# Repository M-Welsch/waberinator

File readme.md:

# Waberinator

Ambient LED driver unit for this guy: https://www.deviantart.com/seggos-artworks

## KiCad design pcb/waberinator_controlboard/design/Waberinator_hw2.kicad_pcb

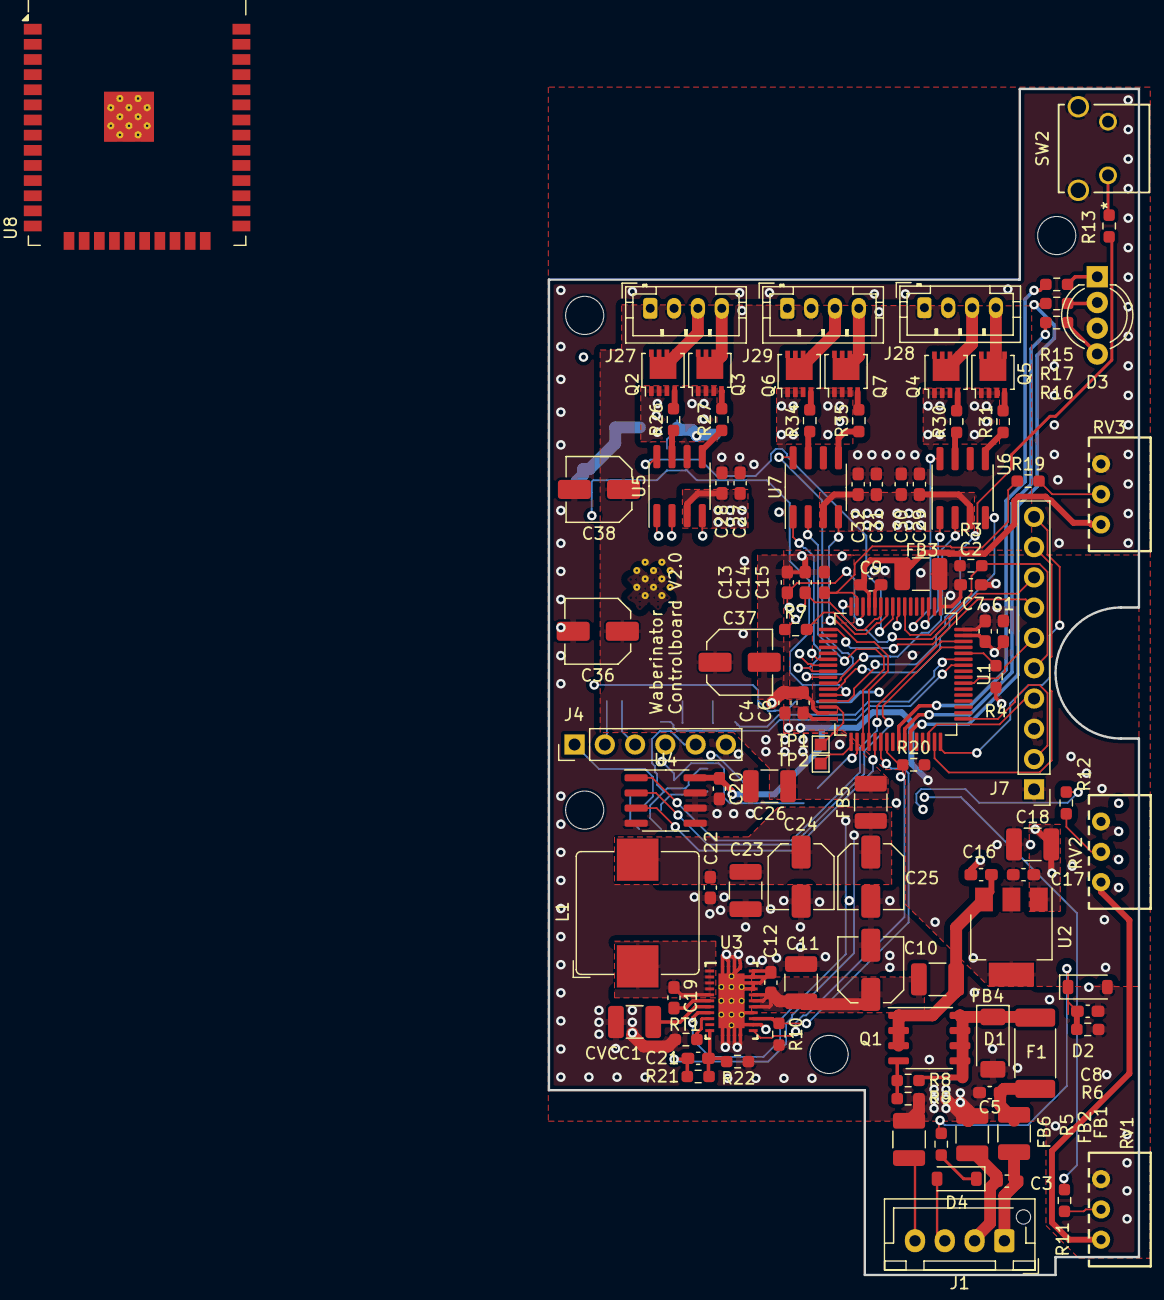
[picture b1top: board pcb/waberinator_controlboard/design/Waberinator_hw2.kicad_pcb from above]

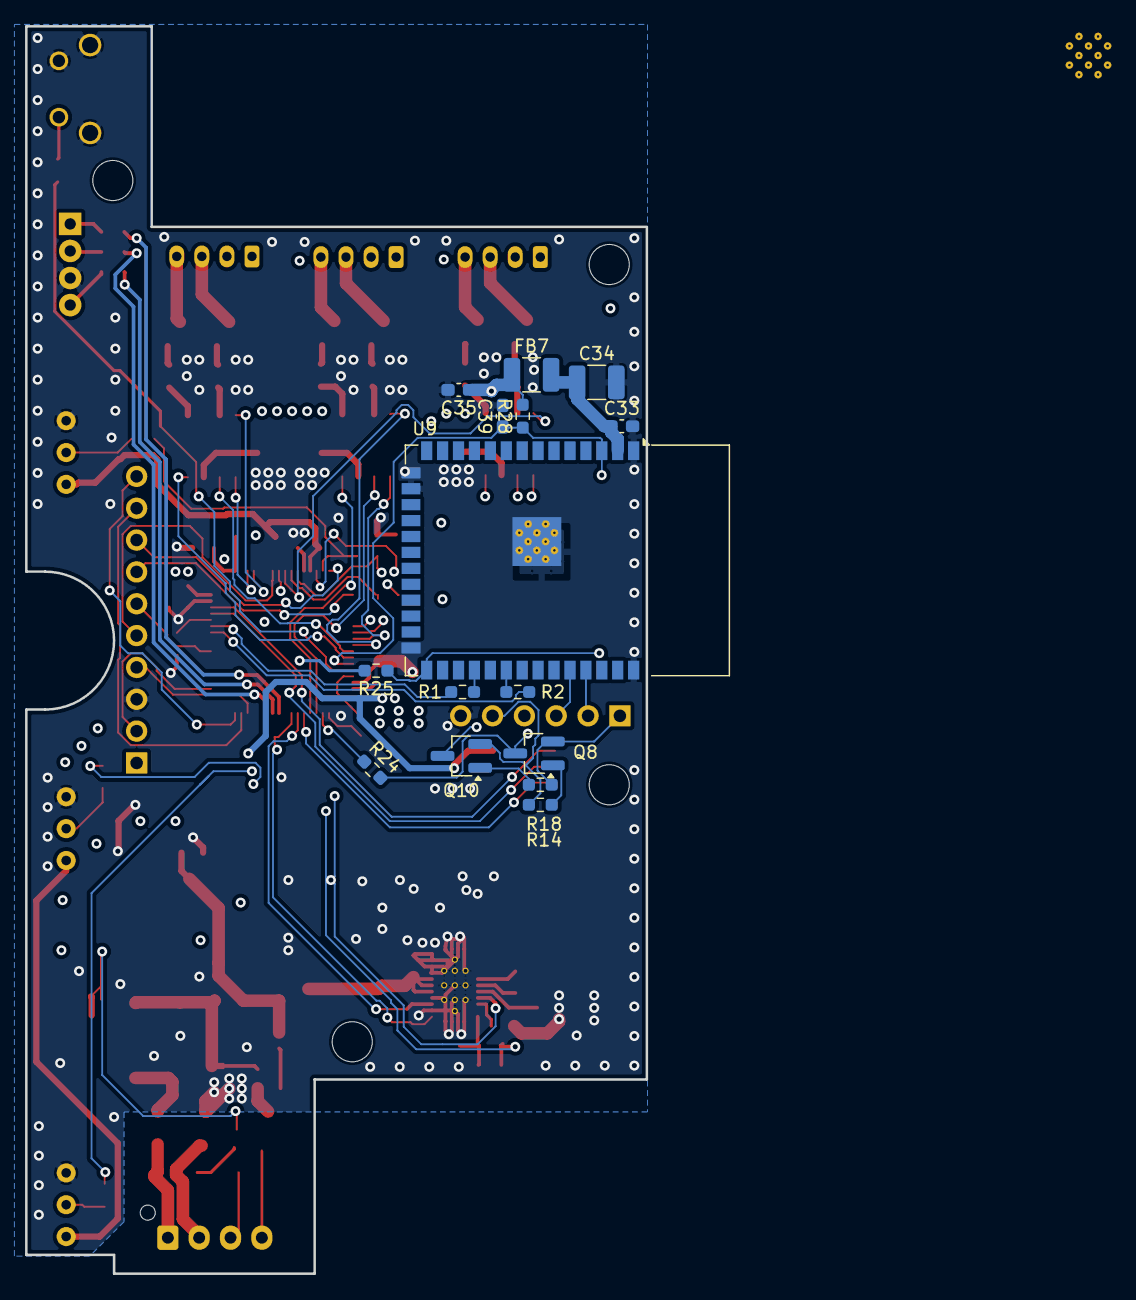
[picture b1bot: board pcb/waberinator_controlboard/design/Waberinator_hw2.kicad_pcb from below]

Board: 4 copper layers, 49.5 x 99.5 mm, 120 parts (15 on the bottom side), 98 nets.

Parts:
C1, C27, C29, C31, C39: 1µF; C_0603_1608Metric_Pad1.08x0.95mm_HandSolder
C2, C4, C6, C7, C8, C9, C16, C17, C20, C28, C30, C32, C33, C35: 100nF; C_0603_1608Metric_Pad1.08x0.95mm_HandSolder
C3, C5: C_0603_1608Metric_Pad1.08x0.95mm_HandSolder
C10, C24, C25, C36, C37, C38: 56µF; C_Elec_5x5.8
C11, C23, C26: 10µF; C_1210_3225Metric_Pad1.33x2.70mm_HandSolder
C12: 47nF; C_0603_1608Metric_Pad1.08x0.95mm_HandSolder
C13, C14, C15: 10n; C_0603_1608Metric_Pad1.08x0.95mm_HandSolder
C18: 22µF; C_1210_3225Metric_Pad1.33x2.70mm_HandSolder
C19, C22: 470nF; C_0603_1608Metric_Pad1.08x0.95mm_HandSolder
C21: 6.8pF; C_0603_1608Metric_Pad1.08x0.95mm_HandSolder
C34: 100µF; C_1210_3225Metric_Pad1.33x2.70mm_HandSolder
CVCC1: 2.2µF; C_1210_3225Metric_Pad1.33x2.70mm_HandSolder
D1: 824501121; D_SOD-128
D2, D4: SD103CW-E3-08; D_SOD-123
D3: RGB LED; LED_D5.0mm-4_RGB_Wide_Pins
F1: Fuse_2512_6332Metric_Pad1.52x3.35mm_HandSolder
FB1, FB2, FB3, FB4, FB5, FB6, FB7: FerriteBead; C_1210_3225Metric_Pad1.33x2.70mm_HandSolder
H1, H2, H3, H4: MountingHole; MountingHole_3.2mm_M3_DIN965
J1: Conn_01x04_Pin; JST_XH_B4B-XH-AM_1x04_P2.50mm_Vertical
J4: Conn_01x06; PinHeader_1x06_P2.54mm_Vertical
J7: Conn_01x10_Pin; PinHeader_1x10_P2.54mm_Vertical
J27, J28, J29: Conn_01x04; JST_PH_B4B-PH-K_1x04_P2.00mm_Vertical
L1: 744325330; L_Bourns_SRP1038C_10.0x10.0mm
NT2: NetTie_2; NetTie-2_SMD_Pad0.5mm
Q1: AOSP21321; SO-8_3.9x4.9mm_P1.27mm
Q2, Q3, Q4, Q5, Q6, Q7: SISHA04DN-T1-GE3; LFPAK33
Q8, Q10: Q_NPN_BEC; SOT-23_Handsoldering
R1, R2, R7, R9, R11, R12, R13, R17, R19, R24: 100; R_0603_1608Metric_Pad0.98x0.95mm_HandSolder
R3, R4, R5, R8, R10, R20, R21: 100k; R_0603_1608Metric_Pad0.98x0.95mm_HandSolder
R6: 24,9k; R_0603_1608Metric_Pad0.98x0.95mm_HandSolder
R14, R18, R28: 10k; R_0603_1608Metric_Pad0.98x0.95mm_HandSolder
R15, R16: 120; R_0603_1608Metric_Pad0.98x0.95mm_HandSolder
R22: 14.3k; R_0603_1608Metric_Pad0.98x0.95mm_HandSolder
R25: 5k; R_0603_1608Metric_Pad0.98x0.95mm_HandSolder
R26, R27, R30, R31, R34, R35: 1; R_0603_1608Metric_Pad0.98x0.95mm_HandSolder
RT1: 95k3; R_0603_1608Metric_Pad0.98x0.95mm_HandSolder
RV1: Brightness; poti_3310C-025-103L
RV2: Frequency; poti_3310C-025-103L
RV3: Depth; poti_3310C-025-103L
SW2: sw_te_1-1825027-1
TP1, TP2: TestPoint; TestPoint_Pad_1.0x1.0mm
U1: STM32F030R8Tx; LQFP-64_10x10mm_P0.5mm
U2: AMS1117-3.3; SOT-223-3_TabPin2
U3: LM73606QRNPRQ1; 30-WFQFN-RNP0030A
U4: LM75B; SOIC-8_3.9x4.9mm_P1.27mm
U5, U6, U7: MCP14A0304xMNY; SOIC-8_3.9x4.9mm_P1.27mm
U8: ESP32-WROOM-32
U9: ESP32-S3-WROOM-1

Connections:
+3.3VA: C9.1, FB3.2, RV1.1, RV2.1, RV3.1, U1.13 (VDDA)
+3V3: C1.1, C2.1, C4.1, C6.1, C7.1, C17.1, C18.1, C20.1, C35.1, FB3.1, FB7.1, J7.1, R3.1, R20.2, R25.2, R28.2, U1.1 (VDD), U1.32 (VDD), U1.64 (VDD), U2.2 (VO), U4.8 (+Vs)
/DC_IN+: C3.2, FB1.1, J1.1
/DC_IN-: C3.1, FB2.1, J1.2
/DC_prefuse: C5.1, F1.2, FB1.2
/DC_preprot: D1.1 (A1), F1.1, NT2.2, Q1.5 (D), Q1.6 (D), Q1.7 (D), Q1.8 (D)
/DC_prot: C16.1, FB4.1, Q1.1 (S), Q1.2 (S), Q1.3 (S), U2.3 (VI)
/Two Strings1/gate_a: Q4.4 (G), R30.2
/Two Strings1/gate_b: Q5.4 (G), R31.2
/Two Strings1/low_a: J28.3, Q4.5 (D)
/Two Strings1/low_b: J28.4, Q5.5 (D)
/Two Strings1/out_a: R30.1, U6.7 (OUTA)
/Two Strings1/out_b: R31.1, U6.5 (OUTB)
/Two Strings2/gate_a: Q6.4 (G), R34.2
/Two Strings2/gate_b: Q7.4 (G), R35.2
/Two Strings2/low_a: J29.3, Q6.5 (D)
/Two Strings2/low_b: J29.4, Q7.5 (D)
/Two Strings2/out_a: R34.1, U7.7 (OUTA)
/Two Strings2/out_b: R35.1, U7.5 (OUTB)
/Two Strings/gate_a: Q2.4 (G), R26.2
/Two Strings/gate_b: Q3.4 (G), R27.2
/Two Strings/low_a: J27.3, Q2.5 (D)
/Two Strings/low_b: J27.4, Q3.5 (D)
/Two Strings/out_a: R26.1, U5.7 (OUTA)
/Two Strings/out_b: R27.1, U5.5 (OUTB)
/U0RXD_ESP32: J4.3, U9.36 (RXD0)
/U0TXD_ESP32: J4.2, U9.37 (TXD0)
/U1RXD_ESP32: R2.1, U9.11 (IO18)
/U1TXD_ESP32: R1.1, U9.10 (IO17)
/VLed: C26.1, C27.1, C28.1, C29.1, C30.1, C31.1, C32.1, C36.1, C37.1, C38.1, FB5.2, J27.1, J27.2, J28.1, J28.2, J29.1, J29.2, U5.6 (V+), U6.6 (V+), U7.6 (V+)
/adc_brightness: C13.1, R11.1, U1.14 (PA0)
/adc_depth: C15.1, R19.1, U1.15 (PA1)
/adc_frequency: C14.1, R12.1, U1.11 (PC3)
/bat_kelvin+: D4.2 (A), J1.3
/bat_kelvin-: FB6.1, J1.4
/boot0: R4.2, U1.60 (BOOT0)
/button1: R13.1, U1.29 (PB10)
/esp32_en: C39.1, Q10.3 (C), R28.1, U1.28 (PB2), U9.3 (EN)
/esp32_io0: Q8.3 (C), R24.2, R25.1, U9.27 (IO0)
/esp32_prog_dtr: J4.1, Q8.2 (E), R14.1
/esp32_prog_rts: J4.5, Q10.2 (E), R18.1
/esp32_vdd: C33.1, C34.1, FB7.2, U9.2 (3V3)
/i2c1_scl: U1.61 (PB8), U4.2 (SCL)
/i2c1_sda: U1.62 (PB9), U4.1 (SDA)
/ledstring1_drv_en: U1.8 (PC0), U5.1 (ENA)
/ledstring2_drv_en: U1.9 (PC1), U5.8 (ENB)
/ledstring3_drv_en: U1.3 (PC14), U6.1 (ENA)
/ledstring4_drv_en: U1.4 (PC15), U6.8 (ENB)
/ledstring5_drv_en: U1.24 (PC4), U7.1 (ENA)
/ledstring6_drv_en: U1.25 (PC5), U7.8 (ENB)
/lm75b_int: U1.37 (PC6), U4.3 (O.S.)
/lm73606_en: R10.1, U1.38 (PC7), U3.18 (EN)
/lm73606_out: C21.1, C22.1, C23.1, C24.1, C25.1, FB5.1, L1.2, R21.1, U3.8 (BIAS)
/lm73606_pg: R20.1, U1.39 (PC8), U3.16 (PGOOD)
/lm_fb: C21.2, R21.2, R22.1, U3.11 (FB)
/lm_rt: RT1.2, U3.9 (RT)
/lm_sw: C19.2, L1.1, U3.1 (SW), U3.2 (SW), U3.3 (SW), U3.4 (SW), U3.5 (SW)
/lm_vcc: CVCC1.1, U3.7 (VCC)
/lm_vin: C10.1, C11.1, C12.1, FB4.2, U3.20 (VIN), U3.21 (VIN), U3.22 (VIN)
/spare_1: J7.9, U1.47 (PF6)
/spare_2: J7.10, U1.48 (PF7)
/spare_3: TP1.1, U1.30 (PB11)
/spare_4: TP2.1, U1.33 (PB12)
/swd_swo: J7.6, U1.55 (PB3)
/swd_tck: J7.2, U1.49 (PA14)
/swd_tms: J7.4, U1.46 (PA13)
/tim1_ch1_indicator_led1: R15.1, U1.41 (PA8)
/tim1_ch2_indicator_led2: R16.1, U1.42 (PA9)
/tim1_ch3_indicator_led3: R17.1, U1.43 (PA10)
/tim3_ch1_ledstring1: U1.22 (PA6), U5.2 (INA)
/tim3_ch2_ledstring2: U1.23 (PA7), U5.4 (INB)
/tim3_ch3_ledstring3: U1.26 (PB0), U6.2 (INA)
/tim3_ch4_ledstring4: U1.27 (PB1), U6.4 (INB)
/tim15_ch1_ledstring5: U1.35 (PB14), U7.2 (INA)
/tim15_ch2_ledstring6: U1.36 (PB15), U7.4 (INB)
/usart1_rx_mcu: R1.2, U1.59 (PB7)
/usart1_tx_mcu: R2.2, U1.58 (PB6)
/usart2_rx_mcu: J7.7, U1.17 (PA3)
/usart2_tx_mcu: J7.8, U1.16 (PA2)
/vbat_meas: R7.2, U1.10 (PC2)
/~rst: J7.5, R3.2, U1.7 (NRST)
unnamed: C8.1, D2.1 (K), R5.1, R6.2, R7.1
unnamed: D3.1 (BA), R15.2
unnamed: D3.4 (GA), R16.2
unnamed: D3.2 (RA), R17.2
unnamed: D4.1 (K), R5.2
unnamed: NT2.1, R8.1
unnamed: Q1.4 (G), R8.2, R9.1
unnamed: Q8.1 (B), R18.2
unnamed: Q10.1 (B), R14.2
unnamed: R11.2, RV1.2
unnamed: R12.2, RV2.2
unnamed: R13.2, SW2.1
unnamed: R19.2, RV3.2
unnamed: R24.1, U1.34 (PB13)
unnamed: C19.1, U3.6 (CBOOT)
unnamed: U8.1 (GND), U8.15 (GND), U8.38 (GND), U8.39 (GND)
RET: C1.2, C2.2, C4.2, C5.2, C6.2, C7.2, C8.2, C9.2, C10.2, C11.2, C12.2, C13.2, C14.2, C15.2, C16.2, C17.2, C18.2, C20.2, C22.2, C23.2, C24.2, C25.2, C26.2, C27.2, C28.2, C29.2, C30.2, C31.2, C32.2, C33.2, C34.2, C35.2, C36.2, C37.2, C38.2, C39.2, CVCC1.2, D1.2 (A2), D2.2 (A), D3.3 (K), FB2.2, FB6.2, J4.6, J7.3, Q2.1 (S), Q2.2 (S), Q2.3 (S), Q3.1 (S), Q3.2 (S), Q3.3 (S), Q4.1 (S), Q4.2 (S), Q4.3 (S), Q5.1 (S), Q5.2 (S), Q5.3 (S), Q6.1 (S), Q6.2 (S), Q6.3 (S), Q7.1 (S), Q7.2 (S), Q7.3 (S), R4.1, R6.1, R9.2, R10.2, R22.2, RT1.1, RV1.3, RV2.3, RV3.3, SW2.2, SW2.3, SW2.4, U1.12 (VSSA), U1.31 (VSS), U1.63 (VSS), U2.1 (GND), U3.12 (NC), U3.13 (NC), U3.14 (NC), U3.15 (NC), U3.17 (SYNC), U3.19 (AGND), U3.23 (PGND), U3.24 (PGND), U3.25 (PGND), U3.26 (PGND), U3.27 (NC), U3.28 (NC), U3.29 (NC), U3.30 (NC), U3.31 (DAP), U4.4 (GND), U4.5 (A2), U4.6 (A1), U4.7 (A0), U5.3 (GND), U6.3 (GND), U7.3 (GND), U9.1 (GND), U9.40 (GND), U9.41 (GND)

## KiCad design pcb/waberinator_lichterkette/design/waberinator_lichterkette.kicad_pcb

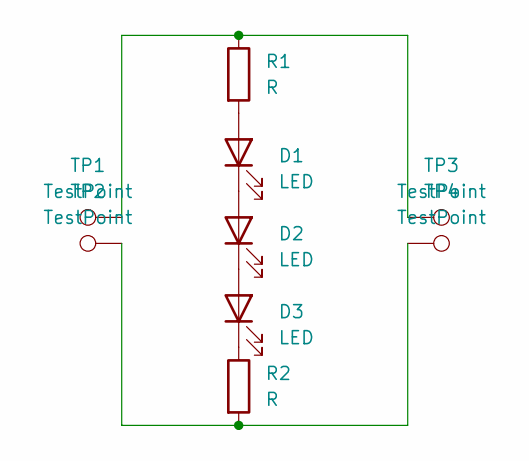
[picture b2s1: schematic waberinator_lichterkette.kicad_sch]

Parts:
D1, D2, D3: LED; LED_1812_4532Metric_Pad1.30x3.40mm_HandSolder
R1, R2: R; R_1210_3225Metric_Pad1.30x2.65mm_HandSolder
TP1, TP2, TP3, TP4: TestPoint; TestPoint_Loop_D3.80mm_Drill2.5mm

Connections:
unnamed: D1.2 (A), R1.2
unnamed: D1.1 (K), D2.2 (A)
unnamed: D2.1 (K), D3.2 (A)
unnamed: D3.1 (K), R2.1
unnamed: R1.1, TP1.1, TP3.1
unnamed: R2.2, TP2.1, TP4.1

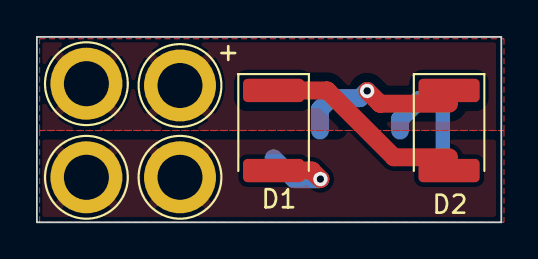
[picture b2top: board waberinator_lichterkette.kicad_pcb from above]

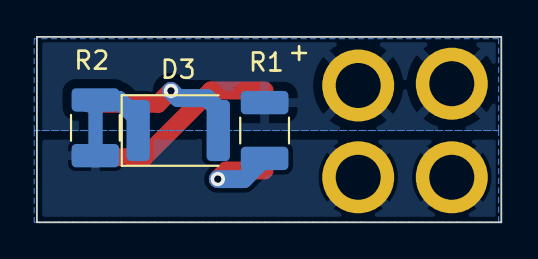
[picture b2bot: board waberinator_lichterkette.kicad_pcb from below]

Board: 2 copper layers, 25.8 x 10.3 mm, 9 parts (3 on the bottom side), 6 nets.

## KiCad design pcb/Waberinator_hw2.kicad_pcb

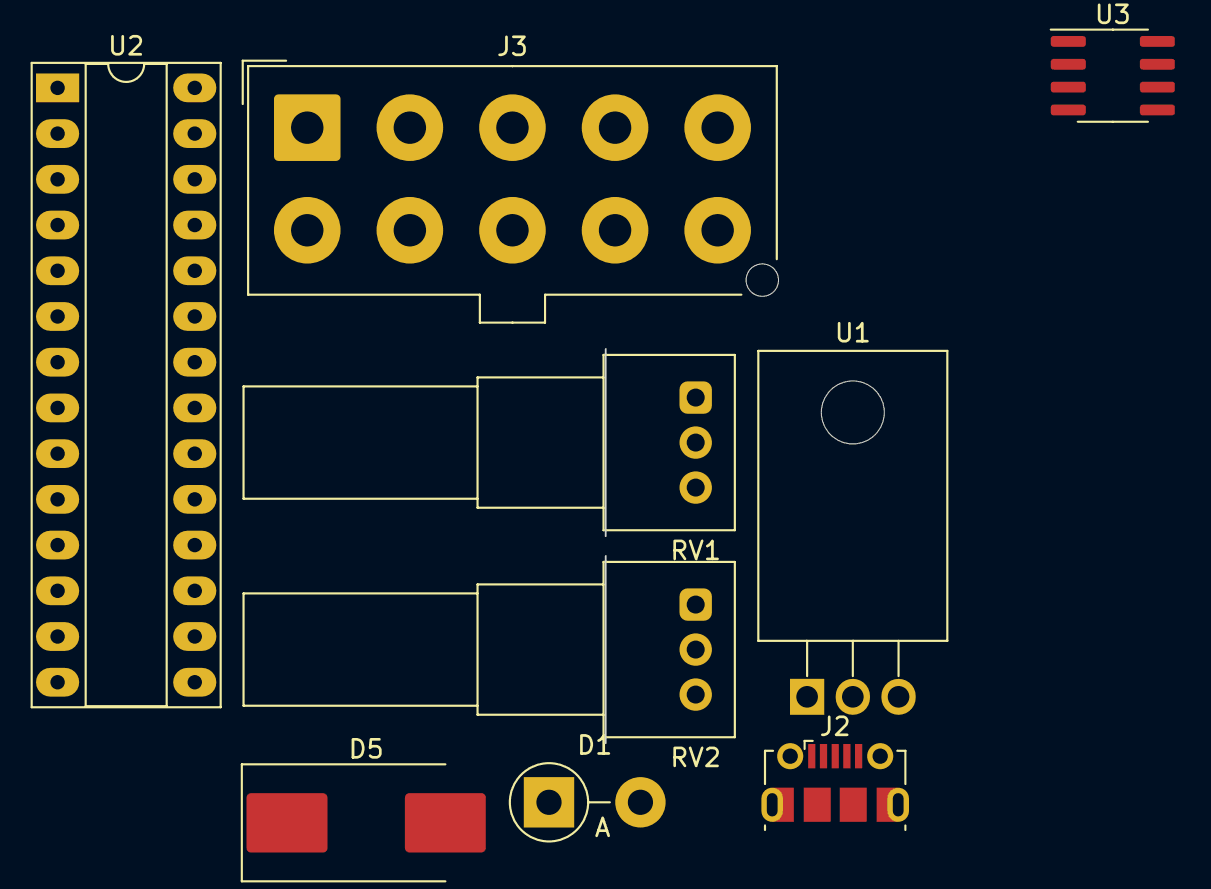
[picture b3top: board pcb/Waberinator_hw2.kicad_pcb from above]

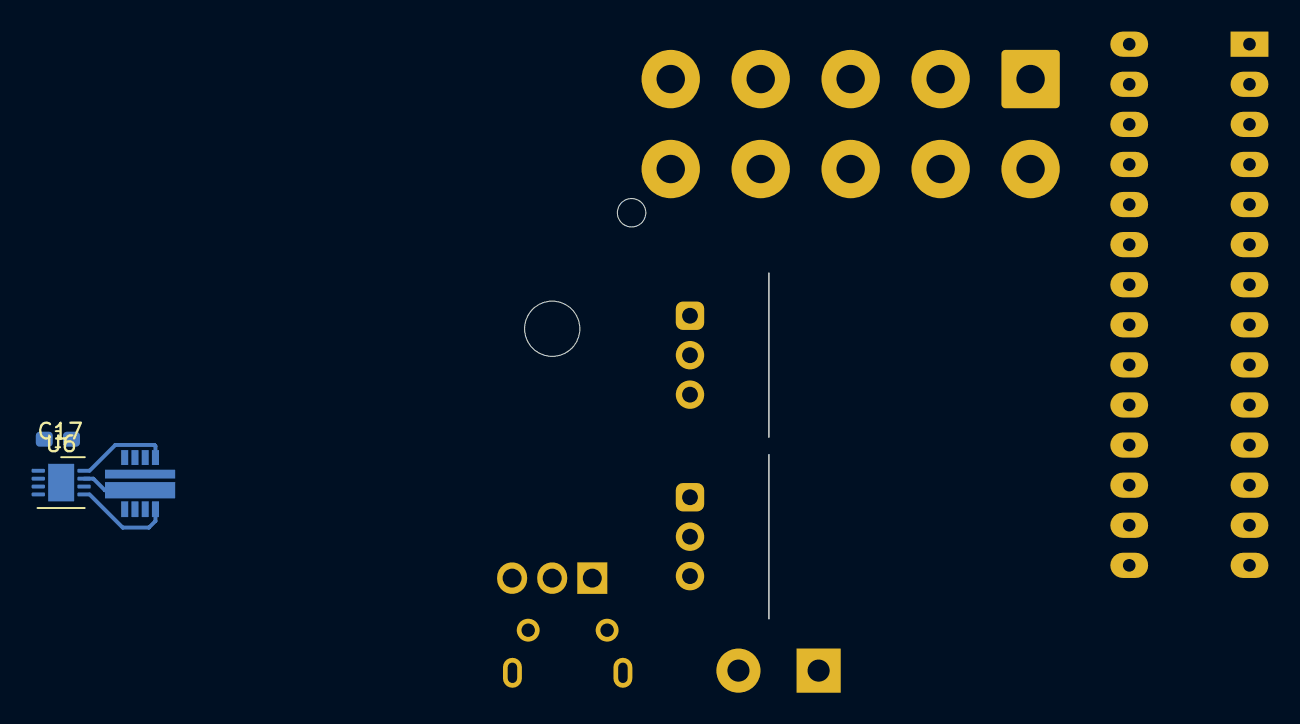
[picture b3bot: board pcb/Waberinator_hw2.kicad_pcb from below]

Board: 2 copper layers, 12 parts (3 on the bottom side), 16 nets.

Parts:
C17: C; C_0603_1608Metric_Pad1.08x0.95mm_HandSolder
D1: D_Schottky; D_5W_P5.08mm_Vertical_AnodeUp
D5: SK34-TP; D_SMC_Handsoldering
J2: USB_OTG; USB_Micro-B_Molex-105017-0001
J3: ISP; Molex_Mega-Fit_76829-0110_2x05_P5.70mm_Vertical
Q1: SiZ340DT; PowerPAIR3x3
RV1: Frequency; Potentiometer_Alps_RK097_Single_Horizontal
RV2: Depth; Potentiometer_Alps_RK097_Single_Horizontal
U1: L7805; TO-220F-3_Horizontal_TabDown
U2: ATMEGA8-16PU; DIP-28_W7.62mm_Socket_LongPads
U3: LM75B; SOIC-8_3.9x4.9mm_P1.27mm
U6: DFN-8-1EP_3x3mm_P0.5mm_EP1.65x2.38mm

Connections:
+5V: D1.2 (A), J2.1 (VBUS), J3.2, RV1.1, RV2.1, U1.3 (OUT), U2.7 (VCC), U2.20 (AVCC), U2.21 (AREF), U3.7 (A0), U3.8 (VCC), U6.4 (VCC)
/Vbat: D1.1 (K), U1.1 (IN)
/Vreg: Q1.2 (D1), Q1.3 (D1), Q1.4 (D1), Q1.10 (D1)
/adc_depth: RV2.2, U2.24 ((ADC1)PC1)
/adc_frequency: RV1.2, U2.23 ((ADC0)PC0)
/bst1: C17.1, U6.1 (BST)
/hg1: Q1.1 (G1), U6.8 (DRVH)
/lg1: Q1.8 (G2), U6.5 (DRVL)
/miso: J3.9, U2.18 ((MISO)PB4)
/mosi: J3.1, U2.17 ((MOSI/OC2)PB3)
/reset: J3.5, U2.1 (PC6(~RESET))
/sck: J3.7, U2.19 ((SCK)PB5)
/scl: U2.28 ((ADC5/SCL)PC5), U3.2 (SCL)
/sda: U2.27 ((ADC4/SDA)PC4), U3.1 (SDA)
/sw1: C17.2, Q1.9 (S1/D2), U6.7 (SW)
GND: D5.2 (A), J2.5 (GND), J2.6 (Shield), J3.8, J3.10, Q1.5 (S2), Q1.6 (S2), Q1.7 (S2), RV1.3, RV2.3, U1.2 (GND), U2.8 (GND), U2.22 (AGND), U3.4 (GND), U3.5 (A2), U3.6 (A1), U6.6 (GND), U6.9 (EP)

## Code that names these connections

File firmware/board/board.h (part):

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/*
 * IO pins assignments.
 */
#define ADC_BRIGHTNESS                0U
#define ADC_DEPTH                1U
#define USART2_TX_MCU                2U
#define USART2_RX_MCU                3U
#define GPIOA_ARD_A2                4U
#define GPIOA_LED_GREEN             5U
#define TIM3_CH1_LEDSTRING1               6U
#define TIM3_CH2_LEDSTRING2               7U
#define TIM1_CH1_INDICATOR_LED_BLUE                8U
#define TIM1_CH2_INDICATOR_LED_GREEN                9U
#define TIM1_CH3_INDICATOR_LED_RED                10U
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#define GPIOA_SWCLK                 14U
#define GPIOA_PIN15                 15U

#define TIM3_CH3_LEDSTRING3                0U
#define TIM3_CH4_LEDSTRING4                  1U
#define MODEM_EN                  2U
#define GPIOB_SWO                   3U
#define GPIOB_ARD_D3                3U
#define GPIOB_ARD_D5                4U
#define GPIOB_ARD_D4                5U
#define USART1_TX_MCU               6U
#define USART1_RX_MCU                  7U
#define I2C1_SCL               8U
#define I2C1_SDA               9U
#define BUTTON                10U
#define SPARE_3                 11U
#define SPARE_4                 12U
#define MODEM_IO0_RESET                 13U
#define TIM15_CH1_LEDSTRING5                 14U
#define TIM15_CH2_LEDSTRING6                 15U

#define LEDSTRING1_DRV_EN                0U
#define LEDSTRING2_DRV_EN                1U
#define VBAT_MEAS                  2U
#define ADC_FREQUENCY                  3U
#define LEDSTRING5_DRV_EN                  4U
#define LEDSTRING6_DRV_EN                  5U
#define GPIOC_PIN6                  6U
#define LM73606_EN                7U
#define LM73606_PG                  8U
#define GPIOC_PIN9                  9U
#define GPIOC_PIN10                 10U
#define GPIOC_PIN11                 11U
#define GPIOC_PIN12                 12U
#define GPIOC_BUTTON                13U
#define LEDSTRING3_DRV_EN              14U
#define LEDSTRING4_DRV_EN             15U

#define GPIOD_PIN0                  0U
#define GPIOD_PIN1                  1U
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#define GPIOF_PIN3                  3U
#define GPIOF_PIN4                  4U
#define GPIOF_PIN5                  5U
#define SPARE_1                  6U
#define SPARE_2                  7U
#define GPIOF_PIN8                  8U
#define GPIOF_PIN9                  9U
#define GPIOF_PIN10                 10U
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#define LINE_ARD_D14                PAL_LINE(GPIOB, 9U)
#define LINE_ARD_D6                 PAL_LINE(GPIOB, 10U)
#define LINE_ARD_A5                 PAL_LINE(GPIOC, 0U)
#define LINE_LEDSTRING1_DRV_EN      PAL_LINE(GPIOC, LEDSTRING1_DRV_EN)
#define LINE_LEDSTRING2_DRV_EN      PAL_LINE(GPIOC, LEDSTRING2_DRV_EN)
#define LINE_LEDSTRING3_DRV_EN      PAL_LINE(GPIOC, LEDSTRING3_DRV_EN)
#define LINE_LEDSTRING4_DRV_EN      PAL_LINE(GPIOC, LEDSTRING4_DRV_EN)
#define LINE_LEDSTRING5_DRV_EN      PAL_LINE(GPIOC, LEDSTRING5_DRV_EN)
#define LINE_LEDSTRING6_DRV_EN      PAL_LINE(GPIOC, LEDSTRING6_DRV_EN)
#define LINE_ADC1_IN10              PAL_LINE(GPIOC, 1U)
#define LINE_LM73606_EN             PAL_LINE(GPIOC, LM73606_EN)
#define LINE_LM73606_PG             PAL_LINE(GPIOC, LM73606_PG)
#define LINE_BUTTON                 PAL_LINE(GPIOB, BUTTON)
#define LINE_OSC32_IN               PAL_LINE(GPIOC, 14U)
#define LINE_OSC32_OUT              PAL_LINE(GPIOC, 15U)
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/*
 * GPIOA setup:
 *
 * PA0  - ARD_A0 ADC1_IN0           (input pullup).
 * PA1  - ARD_A1 ADC1_IN1           (input pullup).
 * PA2  - ARD_D1 USART2_TX          (alternate 1).
 * PA3  - ARD_D0 USART2_RX          (alternate 1).
 * PA4  - ARD_A2 ADC1_IN4           (input pullup).
 * PA5  - LED_GREEN ARD_D13         (output pushpull high).
 * PA6  - ARD_D12                   (input pullup).
 * PA7  - ARD_D11                   (input pullup).
 * PA8  - ARD_D7                    (input pullup).
 * PA9  - ARD_D8                    (input pullup).
 * PA10 - ARD_D2                    (input pullup).
 * PA11 - PIN11                     (input pullup).
 * PA12 - PIN12                     (input pullup).
 * PA13 - SWDIO                     (alternate 0).
 * PA14 - SWCLK                     (alternate 0).
 * PA15 - PIN15                     (input pullup).
 */
#define VAL_GPIOA_MODER             (PIN_MODE_ANALOG(ADC_BRIGHTNESS) |         \
                                     PIN_MODE_ANALOG(ADC_DEPTH) |         \
                                     PIN_MODE_ALTERNATE(USART2_TX_MCU) |     \
                                     PIN_MODE_ALTERNATE(USART2_RX_MCU) |     \
                                     PIN_MODE_INPUT(GPIOA_ARD_A2) |         \
                                     PIN_MODE_OUTPUT(GPIOA_LED_GREEN) |     \
                                     PIN_MODE_ALTERNATE(TIM3_CH1_LEDSTRING1) |        \
                                     PIN_MODE_ALTERNATE(TIM3_CH2_LEDSTRING2) |        \
                                     PIN_MODE_ALTERNATE(TIM1_CH1_INDICATOR_LED_BLUE) |         \
                                     PIN_MODE_ALTERNATE(TIM1_CH2_INDICATOR_LED_GREEN) |         \
                                     PIN_MODE_ALTERNATE(TIM1_CH3_INDICATOR_LED_RED) |         \
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                                     PIN_MODE_ALTERNATE(GPIOA_SWDIO) |      \
                                     PIN_MODE_ALTERNATE(GPIOA_SWCLK) |      \
                                     PIN_MODE_INPUT(GPIOA_PIN15))
#define VAL_GPIOA_OTYPER            (PIN_OTYPE_PUSHPULL(ADC_BRIGHTNESS) |     \
                                     PIN_OTYPE_PUSHPULL(ADC_DEPTH) |     \
                                     PIN_OTYPE_PUSHPULL(USART2_TX_MCU) |     \
                                     PIN_OTYPE_PUSHPULL(USART2_RX_MCU) |     \
                                     PIN_OTYPE_PUSHPULL(GPIOA_ARD_A2) |     \
                                     PIN_OTYPE_PUSHPULL(GPIOA_LED_GREEN) |  \
                                     PIN_OTYPE_PUSHPULL(TIM3_CH1_LEDSTRING1) |    \
                                     PIN_OTYPE_PUSHPULL(TIM3_CH2_LEDSTRING2) |    \
                                     PIN_OTYPE_PUSHPULL(TIM1_CH1_INDICATOR_LED_BLUE) |     \
                                     PIN_OTYPE_PUSHPULL(TIM1_CH2_INDICATOR_LED_GREEN) |     \
                                     PIN_OTYPE_PUSHPULL(TIM1_CH3_INDICATOR_LED_RED) |     \
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                                     PIN_OTYPE_PUSHPULL(GPIOA_SWDIO) |      \
                                     PIN_OTYPE_PUSHPULL(GPIOA_SWCLK) |      \
                                     PIN_OTYPE_PUSHPULL(GPIOA_PIN15))
#define VAL_GPIOA_OSPEEDR           (PIN_OSPEED_HIGH(ADC_BRIGHTNESS) |        \
                                     PIN_OSPEED_HIGH(ADC_DEPTH) |        \
                                     PIN_OSPEED_LOW(USART2_TX_MCU) |         \
                                     PIN_OSPEED_LOW(USART2_RX_MCU) |         \
                                     PIN_OSPEED_HIGH(GPIOA_ARD_A2) |        \
                                     PIN_OSPEED_LOW(GPIOA_LED_GREEN) |      \
                                     PIN_OSPEED_HIGH(TIM3_CH1_LEDSTRING1) |       \
                                     PIN_OSPEED_HIGH(TIM3_CH2_LEDSTRING2) |       \
                                     PIN_OSPEED_HIGH(TIM1_CH1_INDICATOR_LED_BLUE) |        \
                                     PIN_OSPEED_HIGH(TIM1_CH2_INDICATOR_LED_GREEN) |        \
                                     PIN_OSPEED_HIGH(TIM1_CH3_INDICATOR_LED_RED) |        \
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                                     PIN_OSPEED_HIGH(GPIOA_SWDIO) |         \
                                     PIN_OSPEED_HIGH(GPIOA_SWCLK) |         \
                                     PIN_OSPEED_HIGH(GPIOA_PIN15))
#define VAL_GPIOA_PUPDR             (PIN_PUPDR_PULLUP(ADC_BRIGHTNESS) |       \
                                     PIN_PUPDR_PULLUP(ADC_DEPTH) |       \
                                     PIN_PUPDR_FLOATING(USART2_TX_MCU) |     \
                                     PIN_PUPDR_FLOATING(USART2_RX_MCU) |     \
                                     PIN_PUPDR_PULLUP(GPIOA_ARD_A2) |       \
                                     PIN_PUPDR_FLOATING(GPIOA_LED_GREEN) |  \
                                     PIN_PUPDR_PULLUP(TIM3_CH1_LEDSTRING1) |      \
                                     PIN_PUPDR_PULLUP(TIM3_CH2_LEDSTRING2) |      \
                                     PIN_PUPDR_PULLUP(TIM1_CH1_INDICATOR_LED_BLUE) |       \
                                     PIN_PUPDR_PULLUP(TIM1_CH2_INDICATOR_LED_GREEN) |       \
                                     PIN_PUPDR_PULLUP(TIM1_CH3_INDICATOR_LED_RED) |       \
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                                     PIN_PUPDR_PULLUP(GPIOA_SWDIO) |        \
                                     PIN_PUPDR_PULLDOWN(GPIOA_SWCLK) |      \
                                     PIN_PUPDR_PULLUP(GPIOA_PIN15))
#define VAL_GPIOA_ODR               (PIN_ODR_HIGH(ADC_BRIGHTNESS) |           \
                                     PIN_ODR_HIGH(ADC_DEPTH) |           \
                                     PIN_ODR_HIGH(USART2_TX_MCU) |           \
                                     PIN_ODR_HIGH(USART2_RX_MCU) |           \
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
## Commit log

2023-05-29 add readme
2024-01-01 hardware prepared for ebay-lichterketten. Deprecated though
2024-01-01 prepared for stm32f030. Assigned pins for timers and adcs. Selected mosfets and drivers
2024-01-02 progress on schematic
2024-01-04 add lichterkette
2024-02-13 [PCB] components roughly placed
2024-02-17 [HW] draft chassis
2024-02-18 [HW] moved lights connector to top
2024-02-18 [HW] Details
2024-02-20 finalize BOL
2024-02-20 finish chassis
2024-02-22 [HW] pcb production ready
2024-02-23 [HW] finish layout
2024-03-04 [FW] configure board.h
2024-03-04 [HW] misc adjustments to mechanics
2024-03-04 [FW] sketch out serial interface (not tested)
2024-03-05 [FW] first test with serial interface works (hacky)
2024-03-10 trying FreeRTOS
2024-03-10 [FW] shell works
2024-03-11 [FW] implement wabering function
2024-03-11 [FW] implement wabering thread
2024-03-12 [HW/FW] reshape board to get special offer, reassign some pins
2024-03-15 [FW] basic PWM with TIM1 runs
2024-03-15 [FW] wabering parameter control over shell
2024-03-17 [FW] wabering on tim15 works as well
2024-03-17 [FW] enhance shell powers and refactor
2024-03-17 [FW] wabering parameter control over shell enhanced
2024-03-17 [FW] introduce drivers
2024-03-18 [HW] add esp32
2024-03-21 [FW] add uart shell for esp32/modem (not mutexed)
2024-03-21 [FW] remove unused shell thread
2024-03-21 [HW/FW] control power state of modem
2024-04-12 feat(modem): uart2 works
2024-04-12 simple webserver works
2024-04-12 exemplary simple ws server
2024-04-12 ws webserver with spiffs
2024-04-12 webserver with ws and css
2024-04-14 ws works (again)
2024-04-14 slider sends data
2024-04-14 bugfix(mcu): remove race condition with waber_led_cfg o invalid value
2024-04-14 feat(modem): setting brightness works all the line
2024-04-14 feat(modem, mcu): introduce shortform for commands
2024-04-14 feat(mcu, modem): control strings go directly from webapp to mcu
2024-04-15 feat(mcu): refactor to use single config struct
2024-04-16 feat(mcu): implement adc
2024-04-21 [HW] fix esp32 footprint and symbol
2024-04-21 [HW] fix mechanic bugs
2024-04-28 [FW] modem control
2024-04-28 [FW] wabering doesnt work. Not sure why
2024-04-28 [HW] misc changes
2024-04-28 [FW] wabering works again for some reason
2024-05-04 bugfix(chassis): add space for poti o-ring
2024-05-04 bugfix(chassis): add pen-tip-boempel. The thing that is on pens that you can operate touchscreens with
2024-05-04 bugfix(chassis): make space for the led pins and the pushbutton pins
2024-05-04 feat(cableplan): add rudimentary cableplan to driver schematic sheet
2024-05-04 feat(mech): add pockets for orings around gx connectors
2024-05-30 feat(wabering_func): line out maths for frequency change
2024-06-06 [FW] depth and brightness control over potis works
2024-06-06 [FW] getter for adc
2024-06-06 [FW] adjust (not optimize) pwm settings for smoother wabering
2024-07-08 [FW] add uvlo
2024-07-19 [FW] status LED works
2024-07-19 [FW] button integration, button state not correct though
2024-07-20 [FW] optimized PWM, blinks RED on UV
2024-07-20 [FW] add phi adjustment for wabering continuity after frequency change
2024-07-20 [FW] add synchronous mode with depth knob
2024-07-21 [FW] for some reason it doesn't start anymore
2024-07-26 [HW] bugfixes

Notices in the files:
firmware/board/board.h:
ChibiOS - Copyright (C) 2006..2020 Giovanni Di Sirio
Licensed under the Apache License, Version 2.0 (the "License");
